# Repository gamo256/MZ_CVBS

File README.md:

# MZ_CVBS

シャープ　MZ-80(C,K,B)、MZ-1200用　コンポジットビデオ信号とオーディオ信号を出力するための基板

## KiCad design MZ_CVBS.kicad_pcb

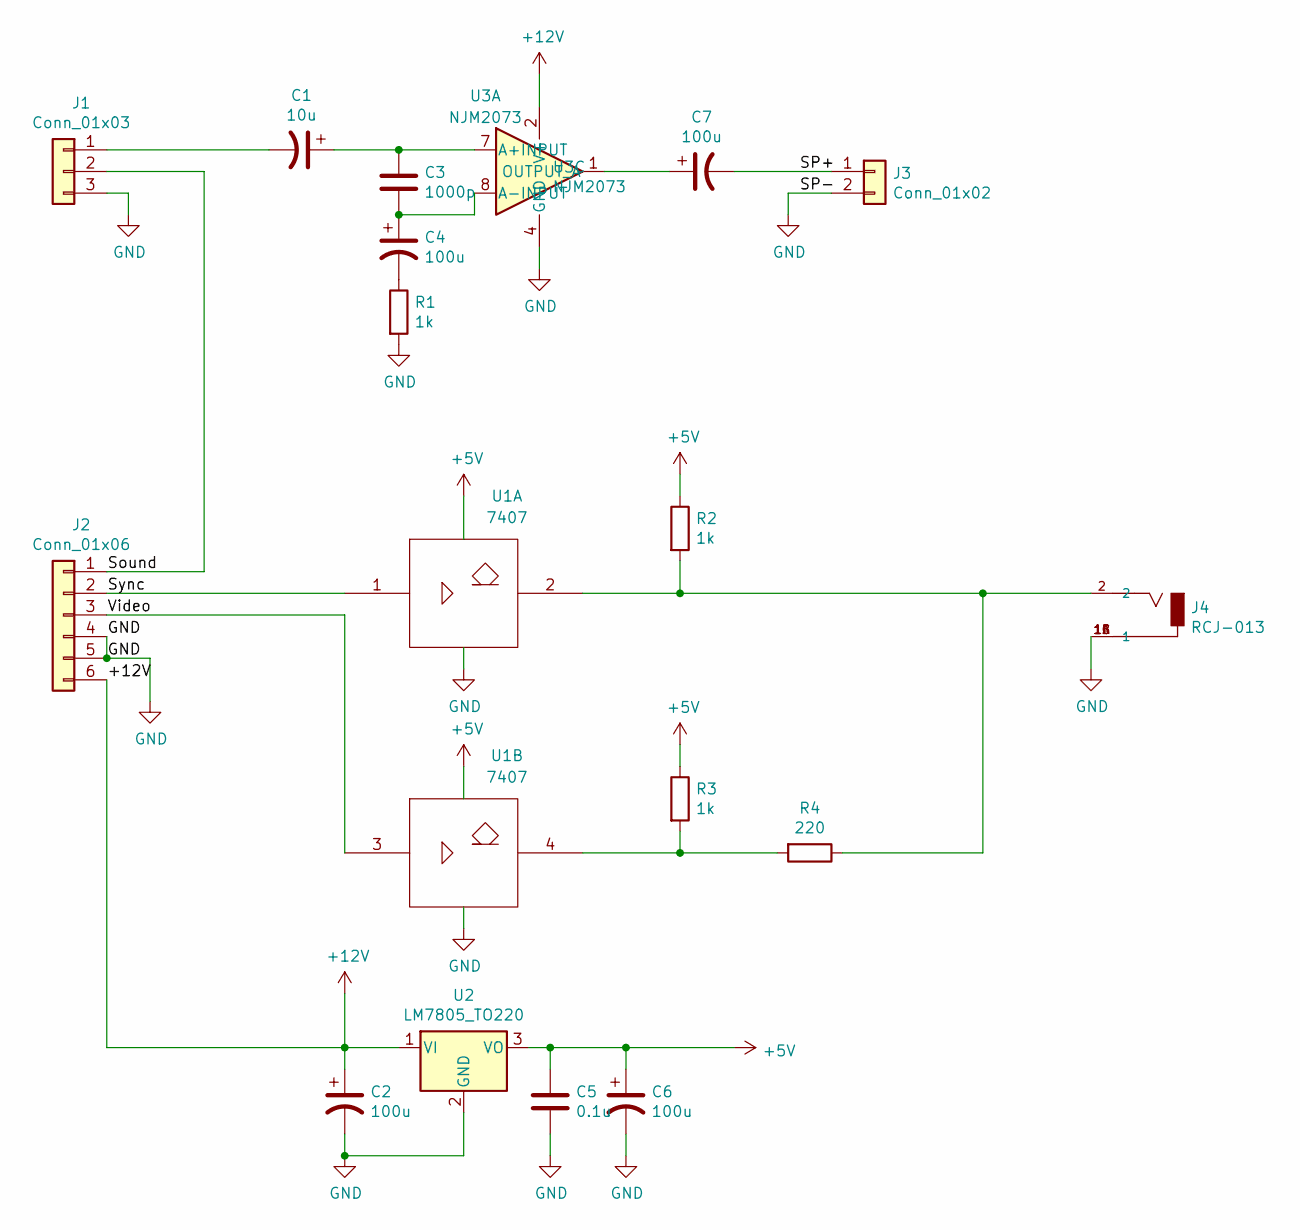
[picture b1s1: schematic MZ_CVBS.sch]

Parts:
C1: 10u; CP_Radial_D4.0mm_P2.00mm
C2, C4, C6, C7: 100u; CP_Radial_D5.0mm_P2.00mm
C3: 1000p; C_Disc_D5.0mm_W2.5mm_P5.00mm
C5: 0.1u; C_Disc_D5.0mm_W2.5mm_P5.00mm
J1: Conn_01x03; PinHeader_1x03_P2.54mm_Vertical
J2: Conn_01x06; PinHeader_1x06_P2.54mm_Vertical
J3: Conn_01x02; PinHeader_1x02_P2.00mm_Horizontal
J4: RCJ-013; CUI_RCJ-013; PART_REV B
R1, R2, R3: 1k; R_Axial_DIN0207_L6.3mm_D2.5mm_P7.62mm_Horizontal
R4: 220; R_Axial_DIN0207_L6.3mm_D2.5mm_P7.62mm_Horizontal
U1: 7407; DIP-14_W7.62mm
U2: LM7805_TO220; TO-220-3_Vertical
U3: NJM2073; DIP-8_W7.62mm

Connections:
+5V: C5.1, C6.1, R2.1, R3.1, U1.14 (Vcc), U2.3 (VO)
+12V: C2.1, J2.6, U2.1 (VI), U3.2 (V+)
/SP+: C7.2, J3.1
/Sound: J1.2, J2.1
/Sync: J2.2, U1.1
/Video: J2.3, U1.3
GND: C2.2, C5.2, C6.2, J1.3, J2.4, J2.5, J3.2, J4.1A (1), J4.1B (1), J4.1C (1), R1.2, U1.7 (Gnd), U2.2 (GND), U3.4 (GND)
unnamed: C1.1, C3.1, U3.7 (A+INPUT)
unnamed: C1.2, J1.1
unnamed: C3.2, C4.1, U3.8 (A-INPUT)
unnamed: C4.2, R1.1
unnamed: C7.1, U3.1 (OUTPUT_A)
unnamed: J4.2, R2.2, R4.1, U1.2
unnamed: R3.2, R4.2, U1.4

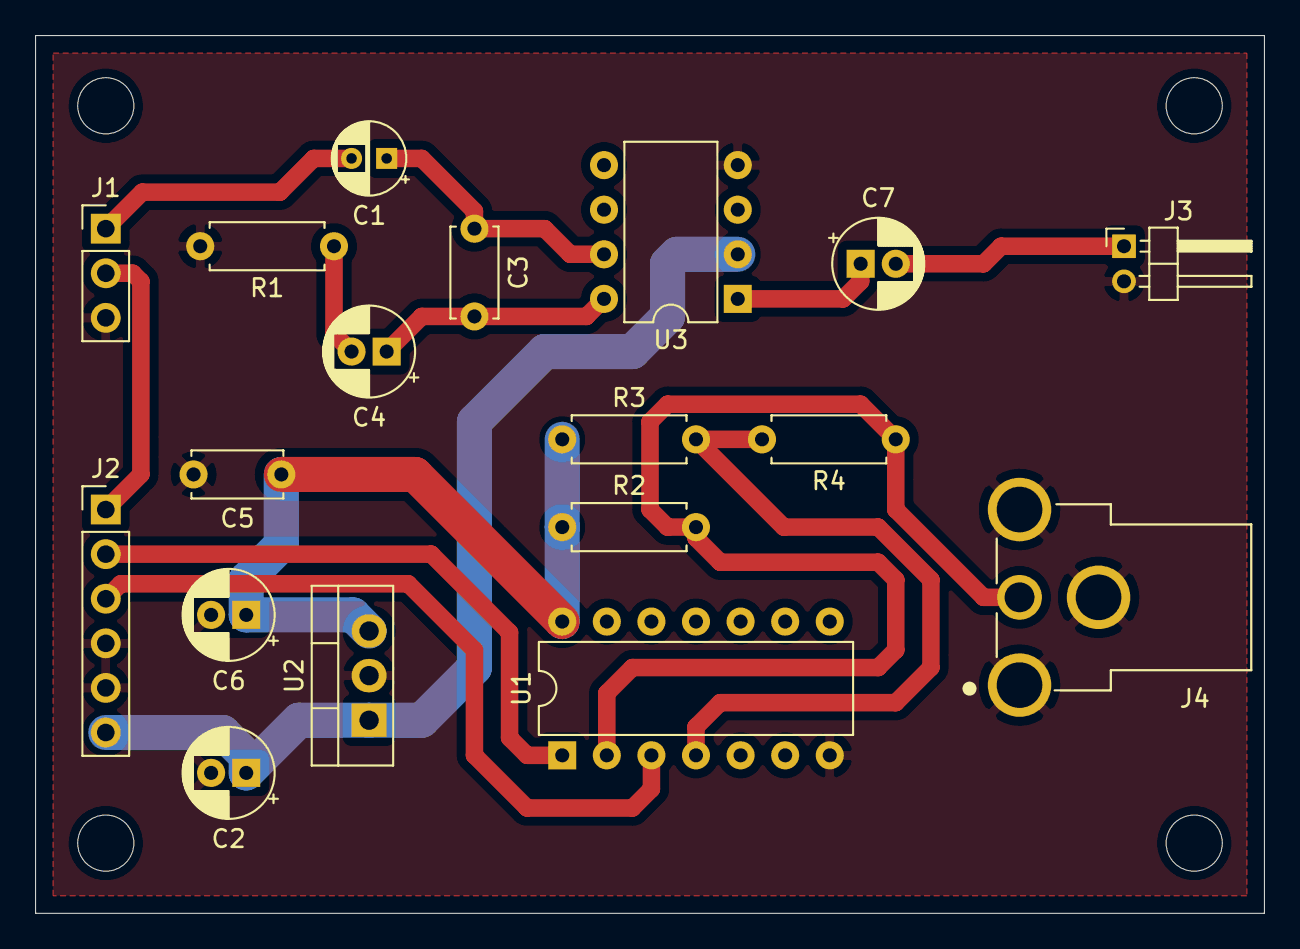
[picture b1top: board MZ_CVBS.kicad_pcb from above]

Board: 2 copper layers, 70.0 x 50.0 mm, 18 parts (0 on the bottom side), 14 nets.
